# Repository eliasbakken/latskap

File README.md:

# latskap
Latskap

8 mm Valchromat, 
- Everything fits within one 2440 x 1220 plate. 
- Wall thickness is 40 mm, giving a discrete thickness of 5 sheets 
- Outer Size: 400x400x400. 
- 45 degree angles on visible joints. 
- 6 mm aluminium arms for strength
- "Nordic triangles" on M6 hex bolts. 

Liquor cabinet, maker-style.

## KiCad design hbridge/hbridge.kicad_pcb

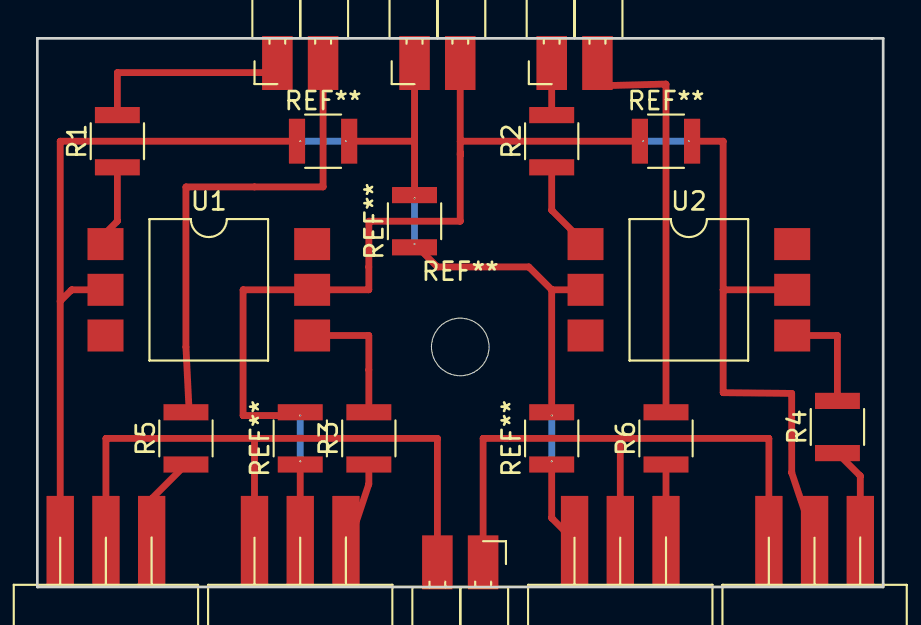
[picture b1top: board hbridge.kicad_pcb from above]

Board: 2 copper layers, 47.0 x 30.5 mm, 16 parts (0 on the bottom side), 16 nets.

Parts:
J1: CONN_A; Pin_Header_Edge_1x02_Pitch2.54mm
J2: CONN_B; Pin_Header_Edge_1x02_Pitch2.54mm
J3: CONN_MOTOR; Pin_Header_Edge_1x02_Pitch2.54mm
J4: CONN_POWER; Pin_Header_Edge_1x02_Pitch2.54mm
Q1, Q2, Q3, Q4: TIP120; TO-220_Horizontal
R1, R2: 470R; R_1210
R3, R4, R5, R6: 1k5; R_1210
U1, U2: OPTO-TRANSISTOR; DIP-6_W11.48mm_SMD

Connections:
/Sheet597E2FB2/AH: J1.1, R1.2
/Sheet597E2FB2/AL: J1.2, R5.2
/Sheet597E2FB2/BH: J2.1, R2.2
/Sheet597E2FB2/BL: J2.2, R6.2
/Sheet597E2FB2/OUTA: J3.2, Q1.3, Q2.2
/Sheet597E2FB2/OUTB: J3.1, Q3.3, Q4.2
Earth: J4.1, Q2.3, Q4.3, U1.2, U2.2
unnamed: Q1.1, R3.1
unnamed: Q2.1, R5.1
unnamed: Q3.1, R4.1
unnamed: Q4.1, R6.1
unnamed: R1.1, U1.1
unnamed: R2.1, U2.1
unnamed: R3.2, U1.4
unnamed: R4.2, U2.4
VPP: J4.2, Q1.2, Q3.2, U1.5, U2.5

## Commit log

2017-07-30 Added Freecad model. Not done yet
2017-07-30 Add schematics for H-bridge driver
2017-07-30 Add Arduino sketch used for testing motor driver
2017-07-30 README: Update oneliner
2017-08-01 almost completed CAD design
2017-08-03 Layed out Valchromat and aluminum
2017-08-05 hbridge: Initial board layout
2017-08-05 hbridge: First PCB made
2017-08-07 hbridge: Smaller board size
2017-08-08 hbridge: Minor update
2017-08-08 Working design before starting animation
2017-08-08 Working animation
2017-08-13 Model for assembly of version 0 finished
